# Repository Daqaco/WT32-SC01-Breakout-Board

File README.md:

# WT32-SC01-Breakout-Board
Breakout board which takes the 2mm header on the display to a 2.54mm header.  Prototyping areas on both sides of the board give additional flexibility.

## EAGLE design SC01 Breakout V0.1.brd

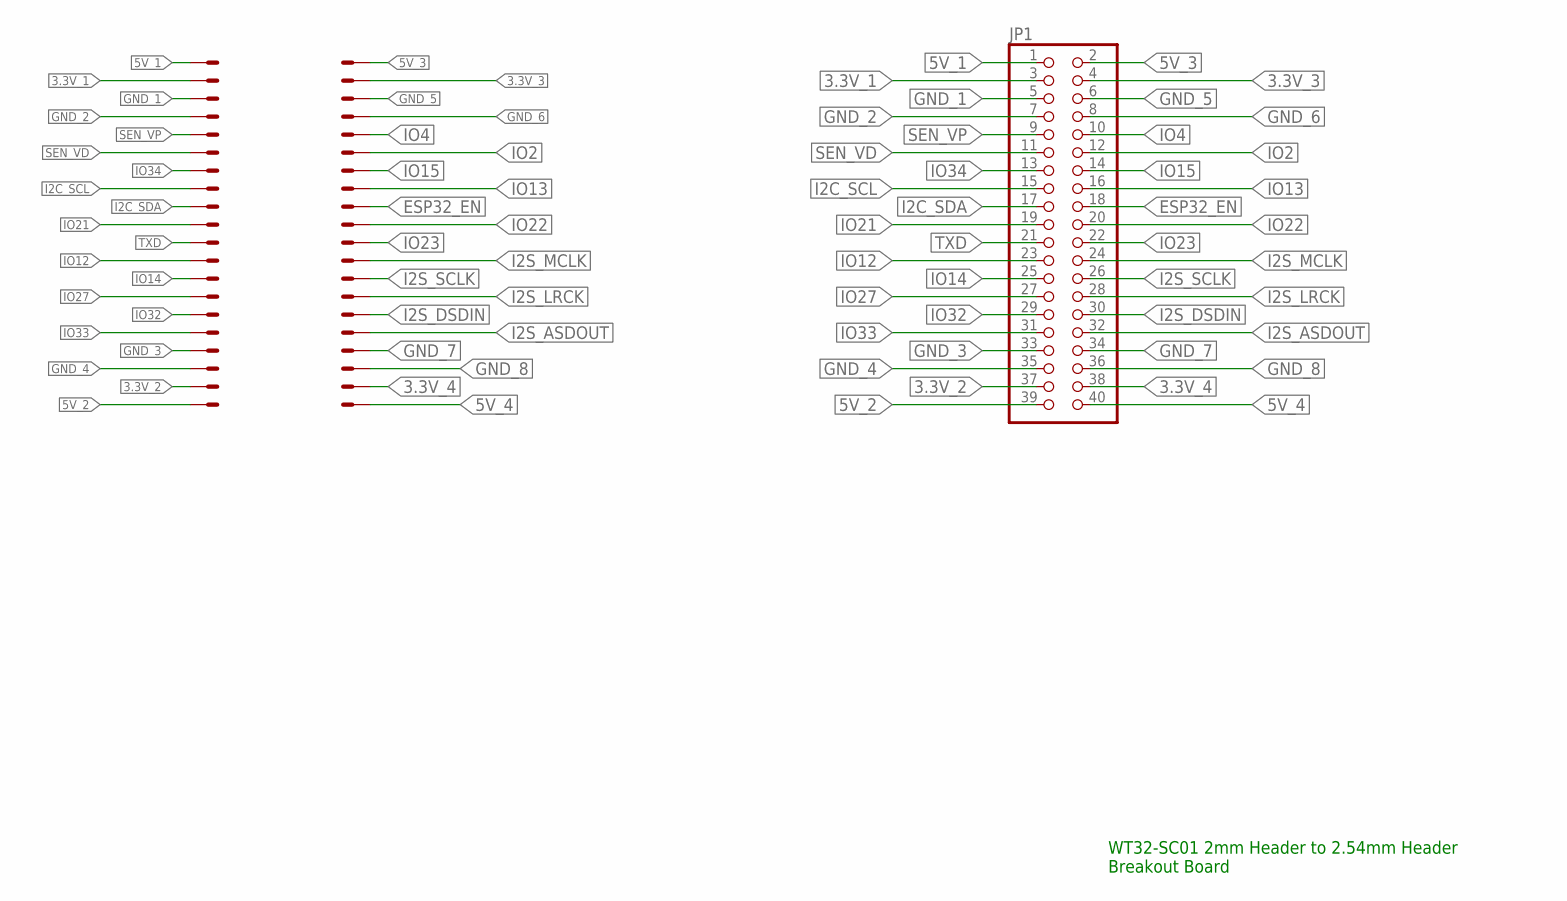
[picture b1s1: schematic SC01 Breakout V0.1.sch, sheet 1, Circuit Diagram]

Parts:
JP1: PINHD-2X20; 2X20
X1: 87758-4016

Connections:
3.3V_1: JP1.3, X1.3
3.3V_2: JP1.37, X1.37
3.3V_3: JP1.4, X1.4
3.3V_4: JP1.38, X1.38
5V_1: JP1.1, X1.1
5V_2: JP1.39, X1.39
5V_3: JP1.2, X1.2
5V_4: JP1.40, X1.40
ESP32_EN: JP1.18, X1.18
GND_1: JP1.5, X1.5
GND_2: JP1.7, X1.7
GND_3: JP1.33, X1.33
GND_4: JP1.35, X1.35
GND_5: JP1.6, X1.6
GND_6: JP1.8, X1.8
GND_7: JP1.34, X1.34
GND_8: JP1.36, X1.36
I2C_SCL: JP1.15, X1.15
I2C_SDA: JP1.17, X1.17
I2S_ASDOUT: JP1.32, X1.32
I2S_DSDIN: JP1.30, X1.30
I2S_LRCK: JP1.28, X1.28
I2S_MCLK: JP1.24, X1.24
I2S_SCLK: JP1.26, X1.26
IO2: JP1.12, X1.12
IO4: JP1.10, X1.10
IO12: JP1.23, X1.23
IO13: JP1.16, X1.16
IO14: JP1.25, X1.25
IO15: JP1.14, X1.14
IO21: JP1.19, X1.19
IO22: JP1.20, X1.20
IO23: JP1.22, X1.22
IO27: JP1.27, X1.27
IO32: JP1.29, X1.29
IO33: JP1.31, X1.31
IO34: JP1.13, X1.13
SEN_VD: JP1.11, X1.11
SEN_VP: JP1.9, X1.9
TXD: JP1.21, X1.21

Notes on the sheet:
WT32-SC01 2mm Header to 2.54mm Header Breakout Board

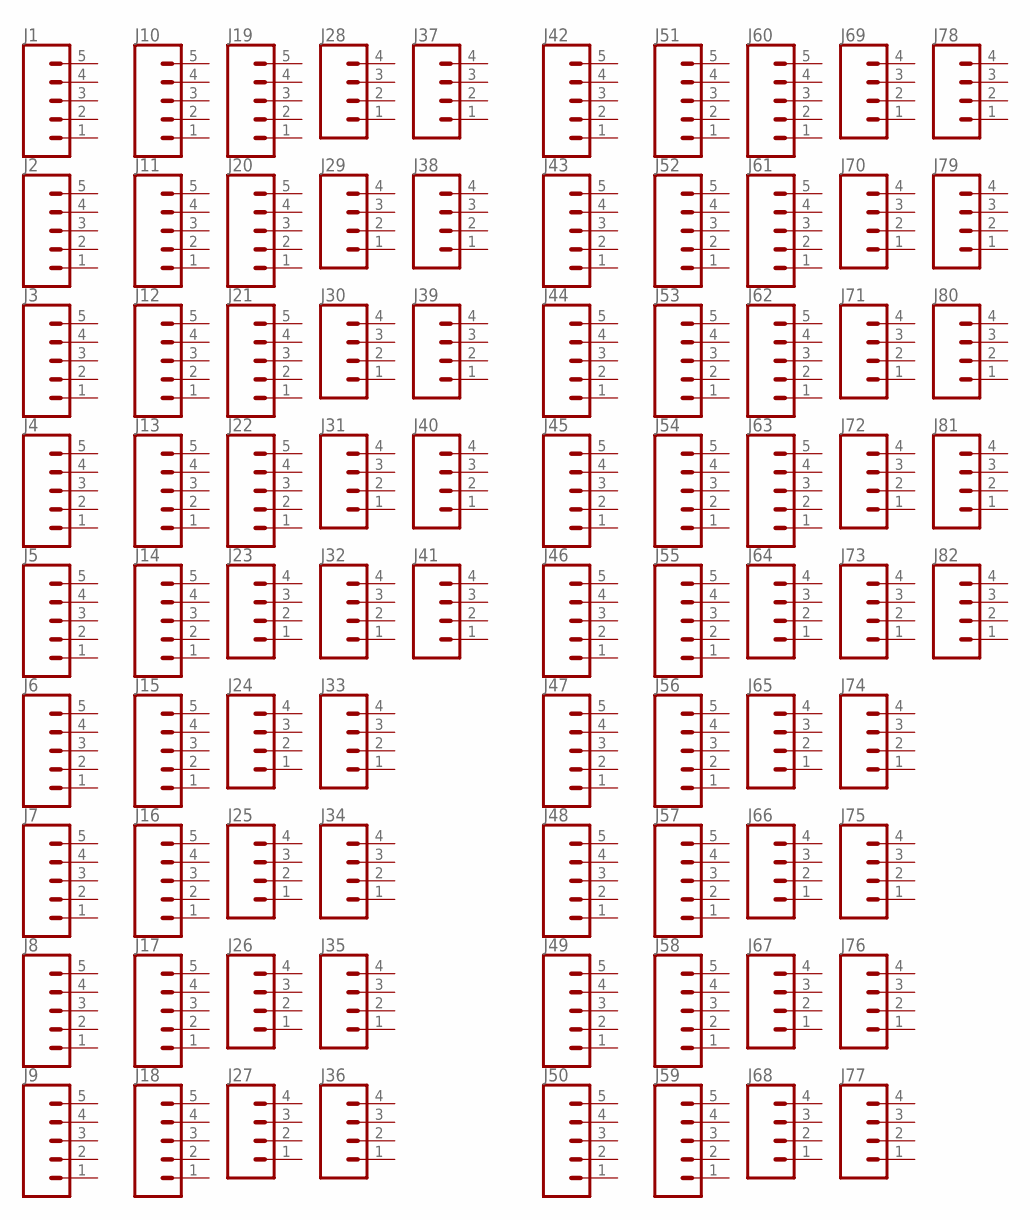
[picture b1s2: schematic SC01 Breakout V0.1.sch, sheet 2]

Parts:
J1, J2, J3, J4, J5, J6, J7, J8, J9, J10, J11, J12, J13, J14, J15, J16, J17, J18, J19, J20, J21, J22, J42, J43, J44, J45, J46, J47, J48, J49, J50, J51, J52, J53, J54, J55, J56, J57, J58, J59, J60, J61, J62, J63: CONN_05NO_SILK; 1X05_NO_SILK
J23, J24, J25, J26, J27, J28, J29, J30, J31, J32, J33, J34, J35, J36, J37, J38, J39, J40, J41, J64, J65, J66, J67, J68, J69, J70, J71, J72, J73, J74, J75, J76, J77, J78, J79, J80, J81, J82: CONN_041X04_NO_SILK; 1X04_NO_SILK

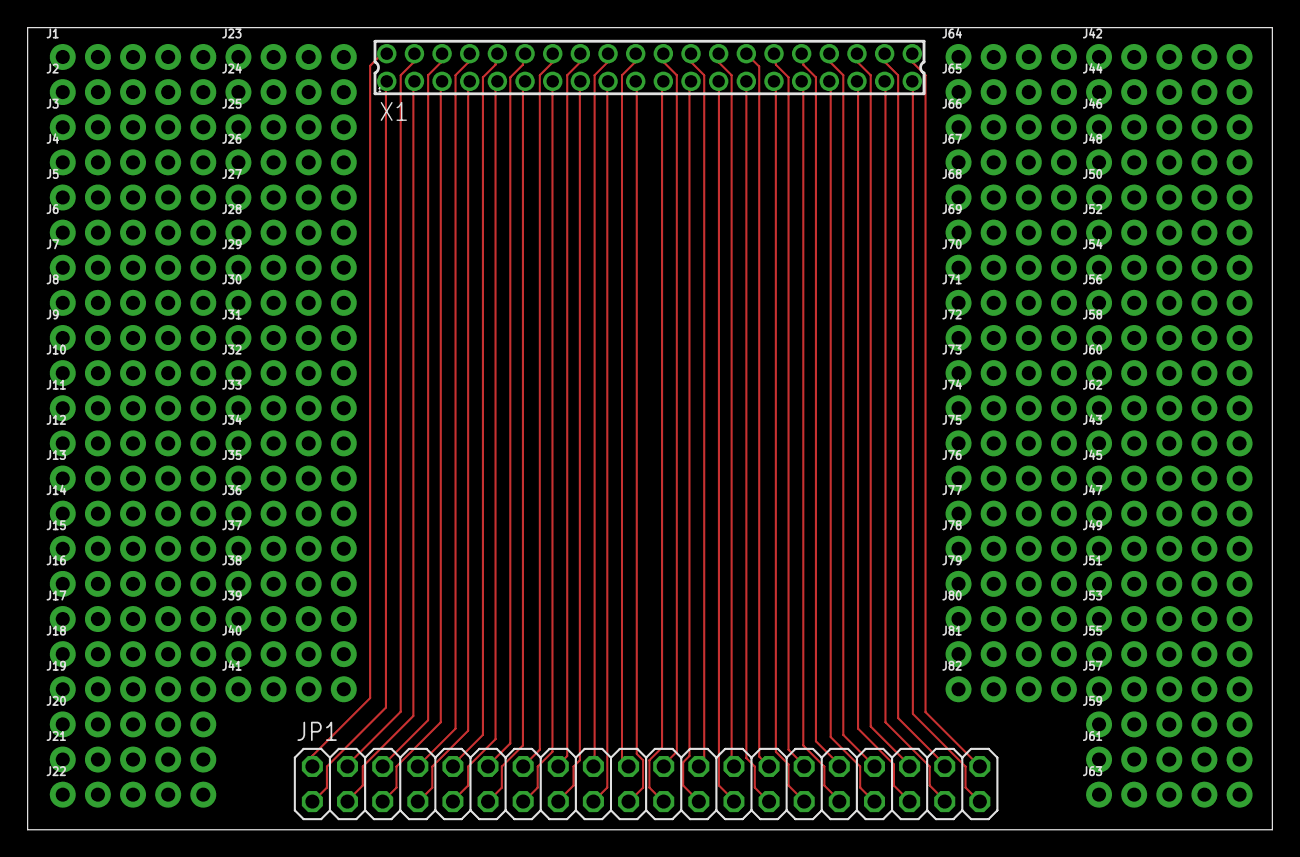
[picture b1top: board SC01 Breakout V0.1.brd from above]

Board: 2 copper layers, 90.0 x 58.0 mm, 84 parts (0 on the bottom side), 40 nets.

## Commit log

2022-02-24 Eagle BRD and SCH files

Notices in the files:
parts and their libraries:
SparkFun-Connectors: Licensing: Creative Commons ShareAlike 4.0 International - https://creativecommons.org/licenses/by-sa/4.0
